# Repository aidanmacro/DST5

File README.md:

---
publishDate: YYYY-MM-DDT00:00:00Z

title: Low-Cost Breath Monitoring for Musicians Using the MYOSA Platform

excerpt: A portable, low-cost respiratory monitoring system for brass and wind musicians using the MYOSA development board, NDIR CO₂ sensing, and environmental measurements.

image: 

tags:
  - Embedded Systems
  - IoT
  - Music Technology
  - Respiratory Monitoring
  - MYOSA
---

> A low-cost embedded system providing objective, real-time respiratory feedback for musicians.

---

## Acknowledgements

---

## Overview

### Project Summary

### Problem Being Solved

### Project Objectives

---

## Demo / Examples

### Images

### Videos

---

## Features (Detailed)

### 1. MYOSA Embedded Platform

### 2. Breath Monitoring System

### 3. BMP180 Environmental Monitoring

### 4. Data Logging

### 5. User Interface

### 6. Low-Cost Design

### 7. Future Improvements

---

## Usage Instructions

### Hardware Setup

### Running the Software

### Example Code

## Tech Stack

---

## Requirements / Installation

### Hardware

### Software

## File Structure (Optional)

---

## License (Optional)

---

## Contribution Notes (Optional)

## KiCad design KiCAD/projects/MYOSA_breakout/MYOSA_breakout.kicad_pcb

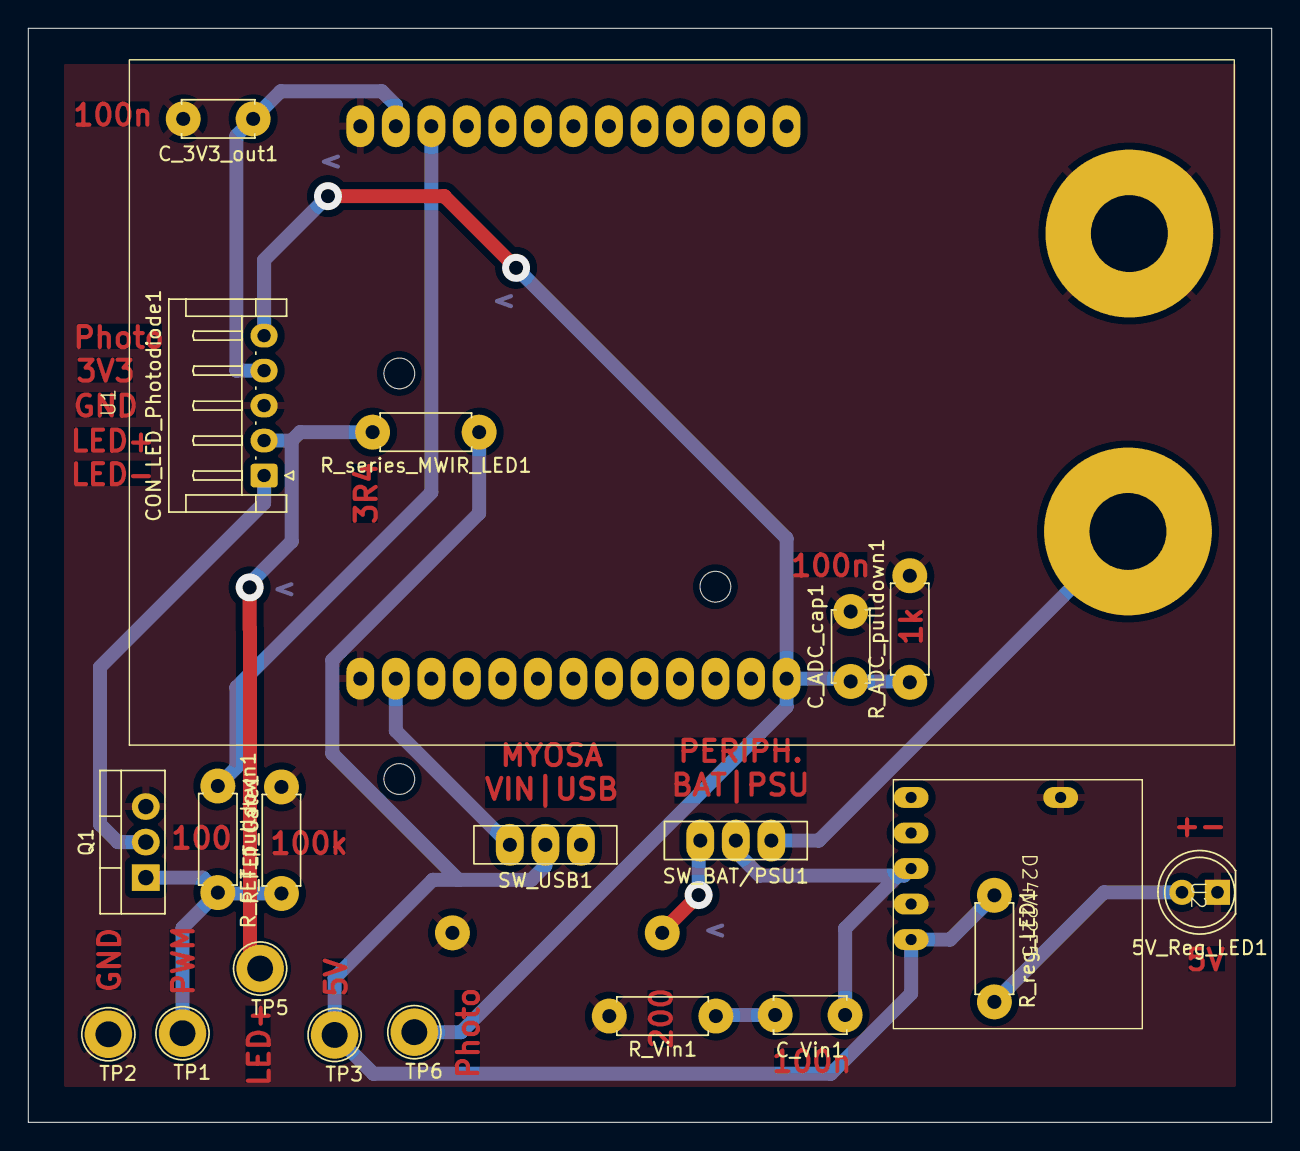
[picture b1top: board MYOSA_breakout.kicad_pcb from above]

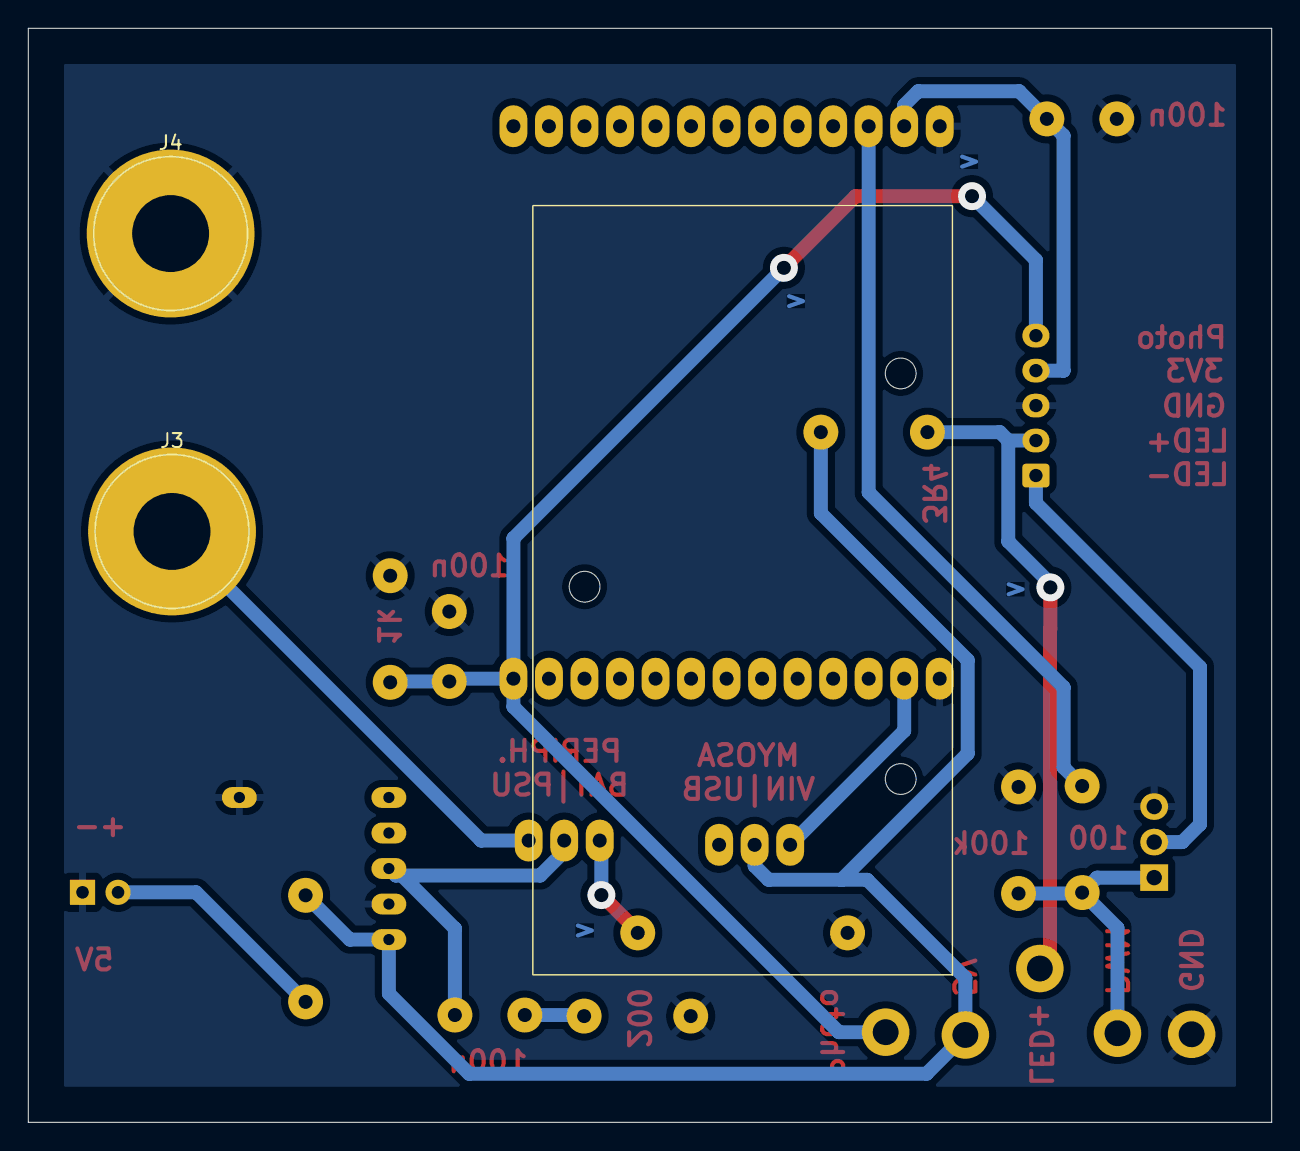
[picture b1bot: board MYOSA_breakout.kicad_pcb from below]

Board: 2 copper layers, 88.9 x 78.2 mm, 24 parts (3 on the bottom side), 14 nets.

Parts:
5V_Reg_LED1: LED; LED_D5.0mm
BT1: Battery; BatteryHolder_MPD_BA9VPC_1xPP3
CON_LED_Photodiode1: Conn_01x05_Socket; JST_EH_S5B-EH_1x05_P2.50mm_Horizontal
C_3V3_out1: C; C_Disc_D5.0mm_W2.5mm_P5.00mm
C_ADC_cap1: 100n; C_Disc_D5.0mm_W2.5mm_P5.00mm
C_Vin1: 100nF; C_Disc_D5.0mm_W2.5mm_P5.00mm
J3: PSU_9V; Banana_Jack_1Pin
J4: PSU_GND; Banana_Jack_1Pin
Q1: IRLZ44N; TO-220-3_Vertical
R_ADC_pulldown1: 1K; R_Axial_DIN0207_L6.3mm_D2.5mm_P7.62mm_Horizontal
R_FET_Gate1: 100R; R_Axial_DIN0207_L6.3mm_D2.5mm_P7.62mm_Horizontal
R_FET_pulldown1: 100k; R_Axial_DIN0207_L6.3mm_D2.5mm_P7.62mm_Horizontal
R_Vin1: 200; R_Axial_DIN0207_L6.3mm_D2.5mm_P7.62mm_Horizontal
R_reg_LED1: 200; R_Axial_DIN0207_L6.3mm_D2.5mm_P7.62mm_Horizontal
R_series_MWIR_LED1: 3.4R; R_Axial_DIN0207_L6.3mm_D2.5mm_P7.62mm_Horizontal
SW_BAT/PSU1: Batt/PSU_switch; SW_Slide-03_Wuerth-WS-SLTV_10x2.5x6.4_P2.54mm
SW_USB1: USB/REG_switch; SW_Slide-03_Wuerth-WS-SLTV_10x2.5x6.4_P2.54mm
TP1: PWM_TestPoint; TestPoint_Loop_D2.50mm_Drill1.85mm
TP2: GND_TestPoint; TestPoint_Loop_D2.50mm_Drill1.85mm
TP3: 5V_TestPoint; TestPoint_Loop_D2.50mm_Drill1.85mm
TP5: LED_Anode_TestPoint; TestPoint_Loop_D2.50mm_Drill1.85mm
TP6: PhotoIn_TestPoint; TestPoint_Loop_D2.50mm_Drill1.85mm
U1: MYOSA_ESP-32
U2: D24V22F5

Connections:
/3V3_OUT: CON_LED_Photodiode1.4, C_3V3_out1.1, U1.25 (3V3)
/5V: R_reg_LED1.1, R_series_MWIR_LED1.1, SW_USB1.2 (B), TP3.1, U2.5 (VOUT)
/LED_Anode: CON_LED_Photodiode1.2, R_series_MWIR_LED1.2, TP5.1
/LED_Cathode: CON_LED_Photodiode1.1, Q1.2 (D)
/PWM: R_FET_Gate1.1, U1.24 (D4)
/Photo_IN: CON_LED_Photodiode1.5, C_ADC_cap1.1, R_ADC_pulldown1.1, TP6.1, U1.13 (VP)
/Vin_SRC: C_Vin1.1, SW_BAT/PSU1.2 (B), U2.3 (VIN)
GND: 5V_Reg_LED1.1 (K), BT1.2 (-), CON_LED_Photodiode1.3, C_3V3_out1.2, C_ADC_cap1.2, J4.1, Q1.3 (S), R_ADC_pulldown1.2, R_FET_pulldown1.2, R_Vin1.2, TP2.1, U1.1 (GND), U1.26 (GND), U2.4 (GND), U2.6 (GND)
unnamed: 5V_Reg_LED1.2 (A), R_reg_LED1.2
unnamed: BT1.1 (+), SW_BAT/PSU1.3 (C)
unnamed: C_Vin1.2, R_Vin1.1
unnamed: J3.1, SW_BAT/PSU1.1 (A)
unnamed: Q1.1 (G), R_FET_Gate1.2, R_FET_pulldown1.1, TP1.1
unnamed: SW_USB1.3 (C), U1.2 (VIN)

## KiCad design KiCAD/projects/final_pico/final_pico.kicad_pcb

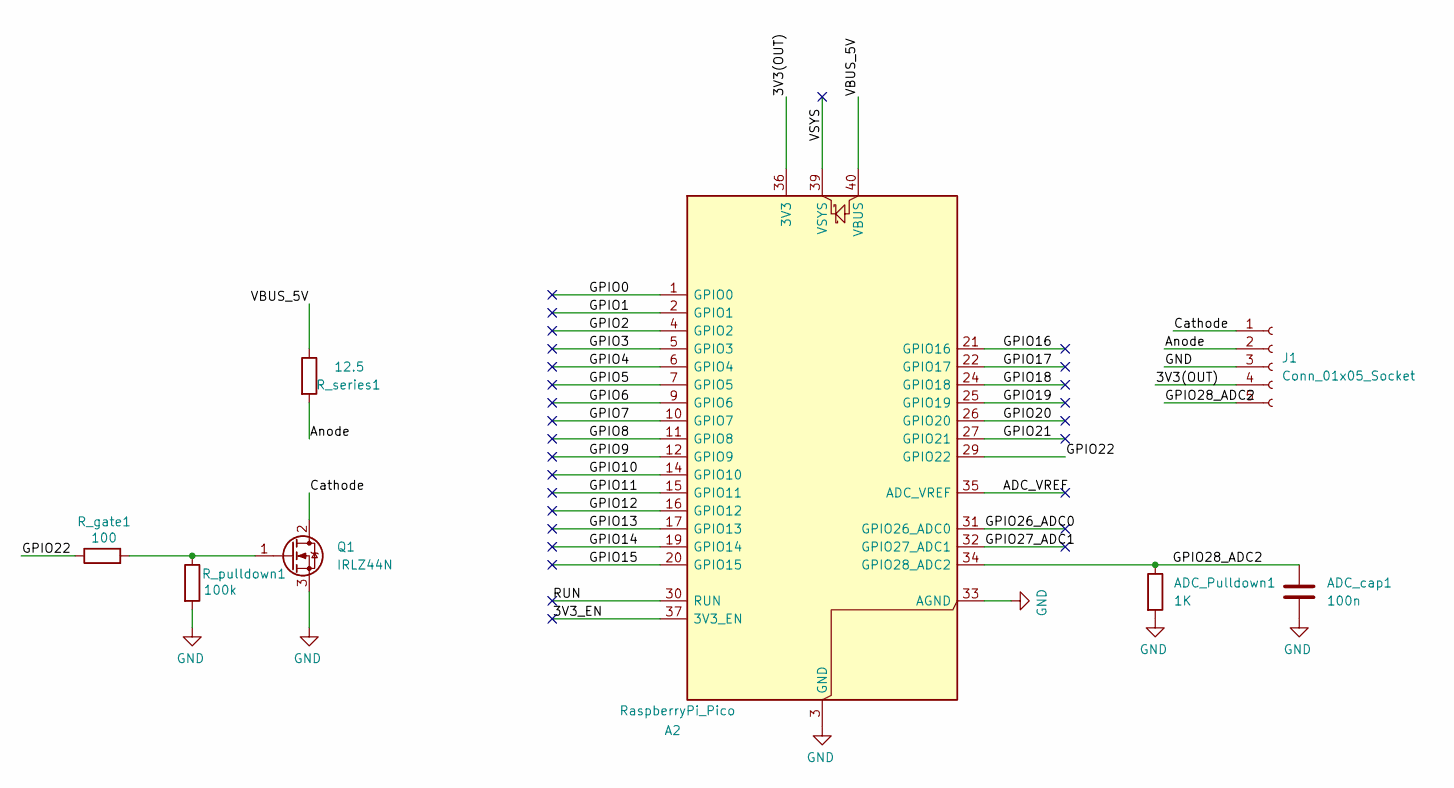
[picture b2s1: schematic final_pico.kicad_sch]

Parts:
A2: RaspberryPi_Pico; RaspberryPi_Pico_Common_THT
ADC_Pulldown1: 1K; R_Axial_DIN0207_L6.3mm_D2.5mm_P7.62mm_Horizontal
ADC_cap1: 100n; C_Disc_D5.0mm_W2.5mm_P5.00mm
J1: Conn_01x05_Socket; JST_EH_S5B-EH_1x05_P2.50mm_Horizontal
Q1: IRLZ44N; TO-220-3_Vertical
R_gate1: 100; R_Axial_DIN0207_L6.3mm_D2.5mm_P7.62mm_Horizontal
R_pulldown1: 100k; R_Axial_DIN0207_L6.3mm_D2.5mm_P7.62mm_Horizontal
R_series1: 12.5; R_Axial_DIN0207_L6.3mm_D2.5mm_P7.62mm_Horizontal

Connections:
/3V3(OUT): A2.36 (3V3), J1.4
/3V3_EN: A2.37 (3V3_EN)
/ADC_VREF: A2.35 (ADC_VREF)
/Anode: J1.2, R_series1.2
/Cathode: J1.1, Q1.2 (D)
/GPIO0: A2.1 (GPIO0)
/GPIO1: A2.2 (GPIO1)
/GPIO2: A2.4 (GPIO2)
/GPIO3: A2.5 (GPIO3)
/GPIO4: A2.6 (GPIO4)
/GPIO5: A2.7 (GPIO5)
/GPIO6: A2.9 (GPIO6)
/GPIO7: A2.10 (GPIO7)
/GPIO8: A2.11 (GPIO8)
/GPIO9: A2.12 (GPIO9)
/GPIO10: A2.14 (GPIO10)
/GPIO11: A2.15 (GPIO11)
/GPIO12: A2.16 (GPIO12)
/GPIO13: A2.17 (GPIO13)
/GPIO14: A2.19 (GPIO14)
/GPIO15: A2.20 (GPIO15)
/GPIO16: A2.21 (GPIO16)
/GPIO17: A2.22 (GPIO17)
/GPIO18: A2.24 (GPIO18)
/GPIO19: A2.25 (GPIO19)
/GPIO20: A2.26 (GPIO20)
/GPIO21: A2.27 (GPIO21)
/GPIO22: A2.29 (GPIO22), R_gate1.1
/GPIO26_ADC0: A2.31 (GPIO26_ADC0)
/GPIO27_ADC1: A2.32 (GPIO27_ADC1)
/GPIO28_ADC2: A2.34 (GPIO28_ADC2), ADC_Pulldown1.1, ADC_cap1.1, J1.5
/RUN: A2.30 (RUN)
/VBUS_5V: A2.40 (VBUS), R_series1.1
/VSYS: A2.39 (VSYS)
GND: A2.3 (GND), A2.8 (GND), A2.13 (GND), A2.18 (GND), A2.23 (GND), A2.28 (GND), A2.33 (AGND), A2.38 (GND), ADC_Pulldown1.2, ADC_cap1.2, J1.3, Q1.3 (S), R_pulldown1.2
unnamed: Q1.1 (G), R_gate1.2, R_pulldown1.1

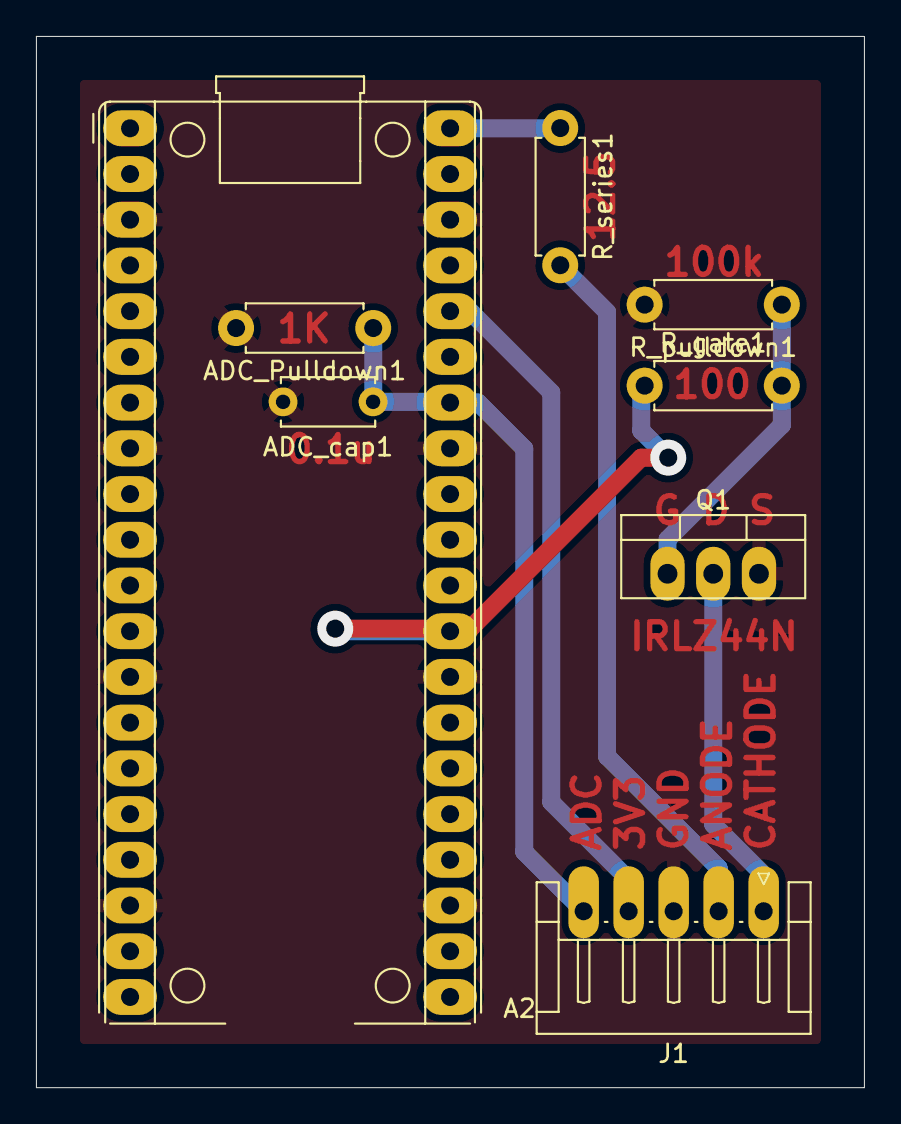
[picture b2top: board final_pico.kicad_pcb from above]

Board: 2 copper layers, 46.0 x 58.4 mm, 8 parts (0 on the bottom side), 8 nets.

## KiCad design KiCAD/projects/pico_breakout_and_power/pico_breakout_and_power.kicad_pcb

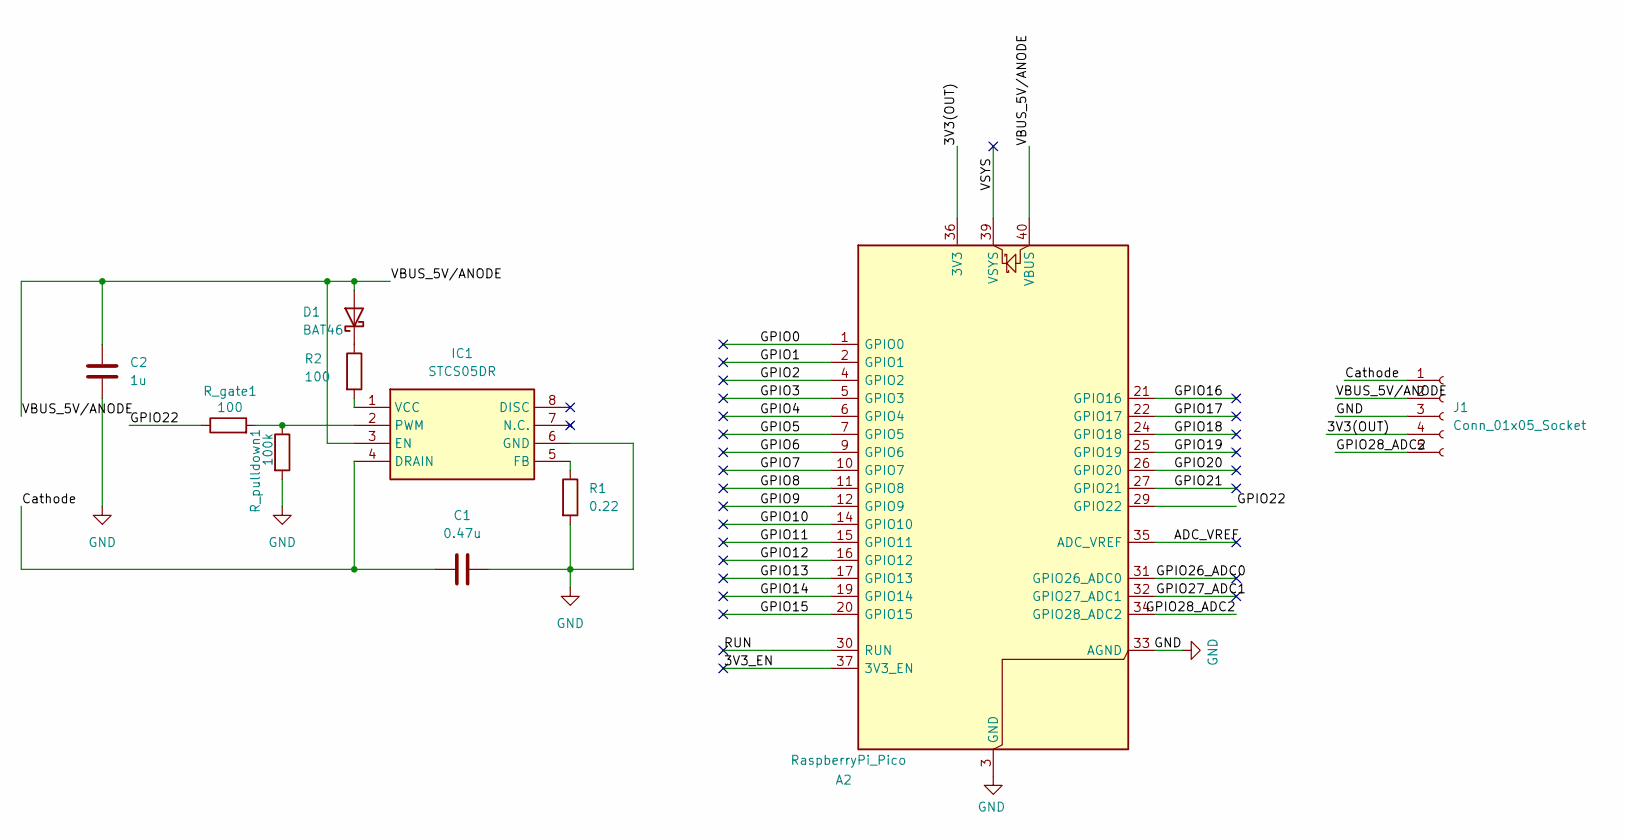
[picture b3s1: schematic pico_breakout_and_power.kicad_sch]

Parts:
A2: RaspberryPi_Pico; RaspberryPi_Pico_Common_THT
C1: 0.47u; C_Disc_D10.5mm_W5.0mm_P10.00mm
C2: 1u; C_Disc_D10.5mm_W5.0mm_P10.00mm
D1: BAT46; D_DO-35_SOD27_P7.62mm_Horizontal
IC1: STCS05DR; SOIC127P600X175-8N; Mouser Part Number 511-STCS05DR
J1: Conn_01x05_Socket; JST_EH_S5B-EH_1x05_P2.50mm_Horizontal
R1: 0.22; R_Axial_DIN0411_L9.9mm_D3.6mm_P12.70mm_Horizontal
R2: 100; R_Axial_DIN0207_L6.3mm_D2.5mm_P10.16mm_Horizontal
R_gate1: 100; R_Axial_DIN0207_L6.3mm_D2.5mm_P10.16mm_Horizontal
R_pulldown1: 100k; R_Axial_DIN0207_L6.3mm_D2.5mm_P10.16mm_Horizontal

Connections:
/3V3(OUT): A2.36 (3V3), J1.4
/3V3_EN: A2.37 (3V3_EN)
/ADC_VREF: A2.35 (ADC_VREF)
/Cathode: C1.1, IC1.4 (DRAIN), J1.1
/GPIO0: A2.1 (GPIO0)
/GPIO1: A2.2 (GPIO1)
/GPIO2: A2.4 (GPIO2)
/GPIO3: A2.5 (GPIO3)
/GPIO4: A2.6 (GPIO4)
/GPIO5: A2.7 (GPIO5)
/GPIO6: A2.9 (GPIO6)
/GPIO7: A2.10 (GPIO7)
/GPIO8: A2.11 (GPIO8)
/GPIO9: A2.12 (GPIO9)
/GPIO10: A2.14 (GPIO10)
/GPIO11: A2.15 (GPIO11)
/GPIO12: A2.16 (GPIO12)
/GPIO13: A2.17 (GPIO13)
/GPIO14: A2.19 (GPIO14)
/GPIO15: A2.20 (GPIO15)
/GPIO16: A2.21 (GPIO16)
/GPIO17: A2.22 (GPIO17)
/GPIO18: A2.24 (GPIO18)
/GPIO19: A2.25 (GPIO19)
/GPIO20: A2.26 (GPIO20)
/GPIO21: A2.27 (GPIO21)
/GPIO22: A2.29 (GPIO22), R_gate1.1
/GPIO26_ADC0: A2.31 (GPIO26_ADC0)
/GPIO27_ADC1: A2.32 (GPIO27_ADC1)
/GPIO28_ADC2: A2.34 (GPIO28_ADC2), J1.5
/RUN: A2.30 (RUN)
/VBUS_5V/ANODE: A2.40 (VBUS), C2.1, D1.2 (A), IC1.3 (EN), J1.2
/VSYS: A2.39 (VSYS)
GND: A2.3 (GND), A2.8 (GND), A2.13 (GND), A2.18 (GND), A2.23 (GND), A2.28 (GND), A2.33 (AGND), A2.38 (GND), C1.2, C2.2, IC1.6 (GND), J1.3, R1.2, R_pulldown1.2
unnamed: D1.1 (K), R2.1
unnamed: IC1.5 (FB), R1.1
unnamed: IC1.2 (PWM), R_gate1.2, R_pulldown1.1
unnamed: IC1.1 (VCC), R2.2

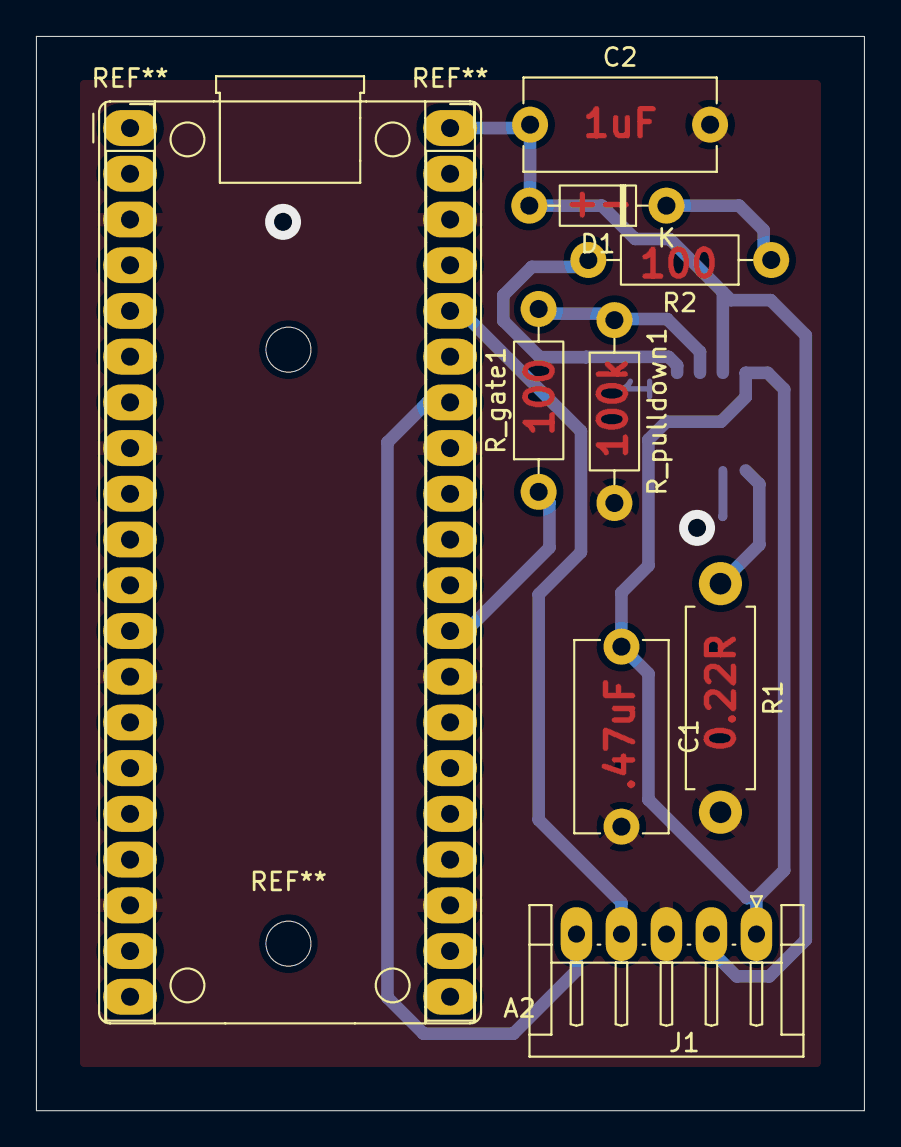
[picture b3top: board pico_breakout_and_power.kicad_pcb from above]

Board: 2 copper layers, 46.0 x 59.7 mm, 10 parts (1 on the bottom side), 10 nets.

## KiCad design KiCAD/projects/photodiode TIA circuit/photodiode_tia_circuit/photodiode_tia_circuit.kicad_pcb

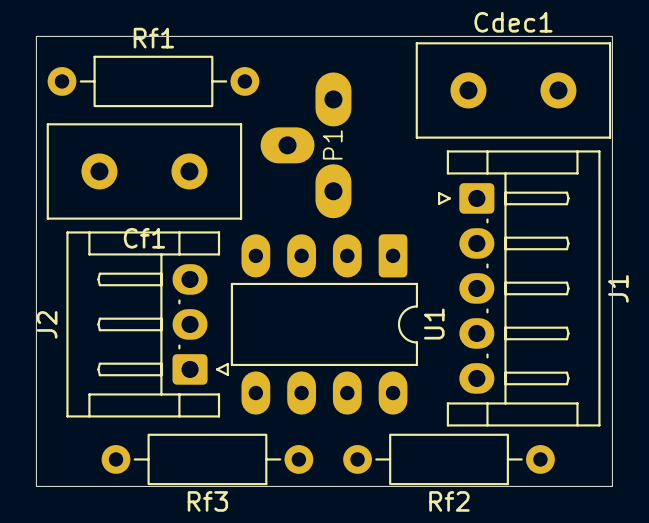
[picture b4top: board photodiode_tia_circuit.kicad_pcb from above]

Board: 2 copper layers, 32.0 x 25.0 mm, 9 parts (0 on the bottom side), 8 nets, no tracks yet.

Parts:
Cdec1: 0.1uF; C_Disc_D10.5mm_W5.0mm_P5.00mm
Cf1: 2pF; C_Disc_D10.5mm_W5.0mm_P5.00mm
J1: Conn_01x05_Socket; JST_EH_S5B-EH_1x05_P2.50mm_Horizontal
J2: Conn_01x03_Socket; JST_EH_S3B-EH_1x03_P2.50mm_Horizontal
P1: TO46_3PIN
Rf1: 470k; R_Axial_DIN0207_L6.3mm_D2.5mm_P10.16mm_Horizontal
Rf2: 100k; R_Axial_DIN0207_L6.3mm_D2.5mm_P10.16mm_Horizontal
Rf3: 1.8k; R_Axial_DIN0207_L6.3mm_D2.5mm_P10.16mm_Horizontal
U1: MCP6292; DIP-8_W7.62mm_LongPads

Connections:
+3.3V: Cdec1.1, J1.4, U1.8 (V+)
GND: Cdec1.2, J1.5, J2.2, P1.2 (GND), P1.3 (Anode), Rf3.2, U1.3 (+), U1.4 (V-)
unnamed: J1.1, J2.3
unnamed: J1.2, J2.1
unnamed: J1.3, Rf2.1, U1.7
unnamed: Cf1.1, P1.1 (Cathode), Rf1.2, U1.2 (-)
unnamed: Cf1.2, Rf1.1, U1.1, U1.5 (+)
unnamed: Rf2.2, Rf3.1, U1.6 (-)

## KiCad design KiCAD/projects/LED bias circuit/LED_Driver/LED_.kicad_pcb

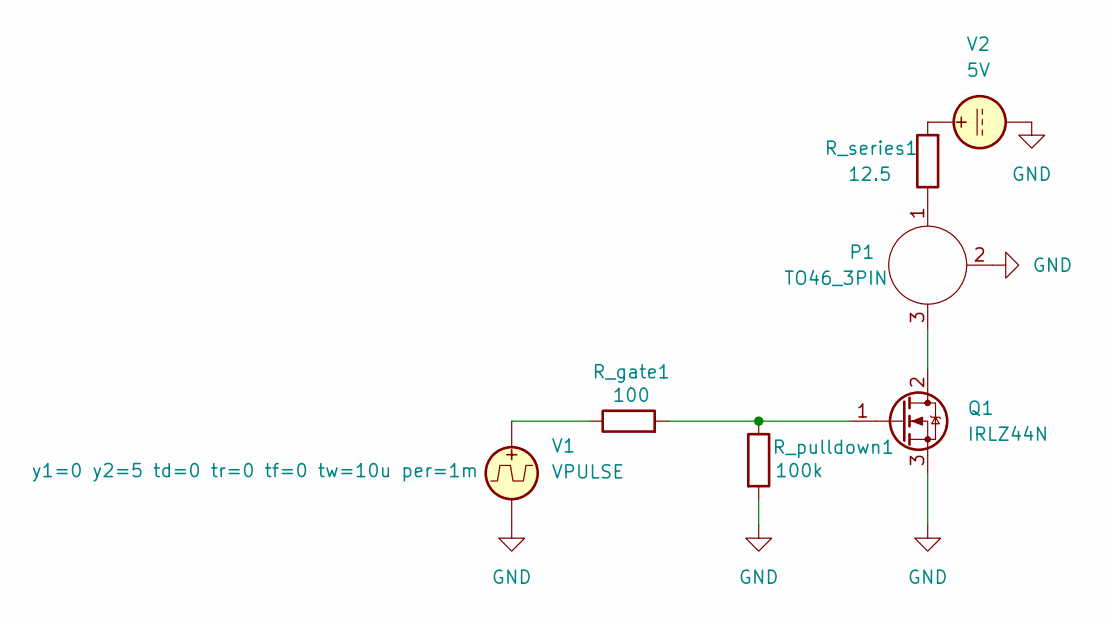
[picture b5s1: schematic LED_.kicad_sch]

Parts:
P1: TO46_3PIN
Q1: IRLZ44N; TO-220-3_Vertical
R_gate1: 100; R_Axial_DIN0207_L6.3mm_D2.5mm_P10.16mm_Horizontal
R_pulldown1: 100k; R_Axial_DIN0207_L6.3mm_D2.5mm_P10.16mm_Horizontal
R_series1: 12.5; R_Axial_DIN0207_L6.3mm_D2.5mm_P10.16mm_Horizontal
V1: VPULSE; TerminalBlock_Phoenix_MKDS-1,5-2-5.08_1x02_P5.08mm_Horizont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
V2: 5V; TerminalBlock_Phoenix_MKDS-1,5-2-5.08_1x02_P5.08mm_Horizont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

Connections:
GND: P1.2 (GND), Q1.3 (S), R_pulldown1.2, V1.2, V2.2
unnamed: P1.1 (Anode), R_series1.1
unnamed: P1.3 (Cathode), Q1.2 (D)
unnamed: Q1.1 (G), R_gate1.2, R_pulldown1.1
unnamed: R_gate1.1, V1.1
unnamed: R_series1.2, V2.1

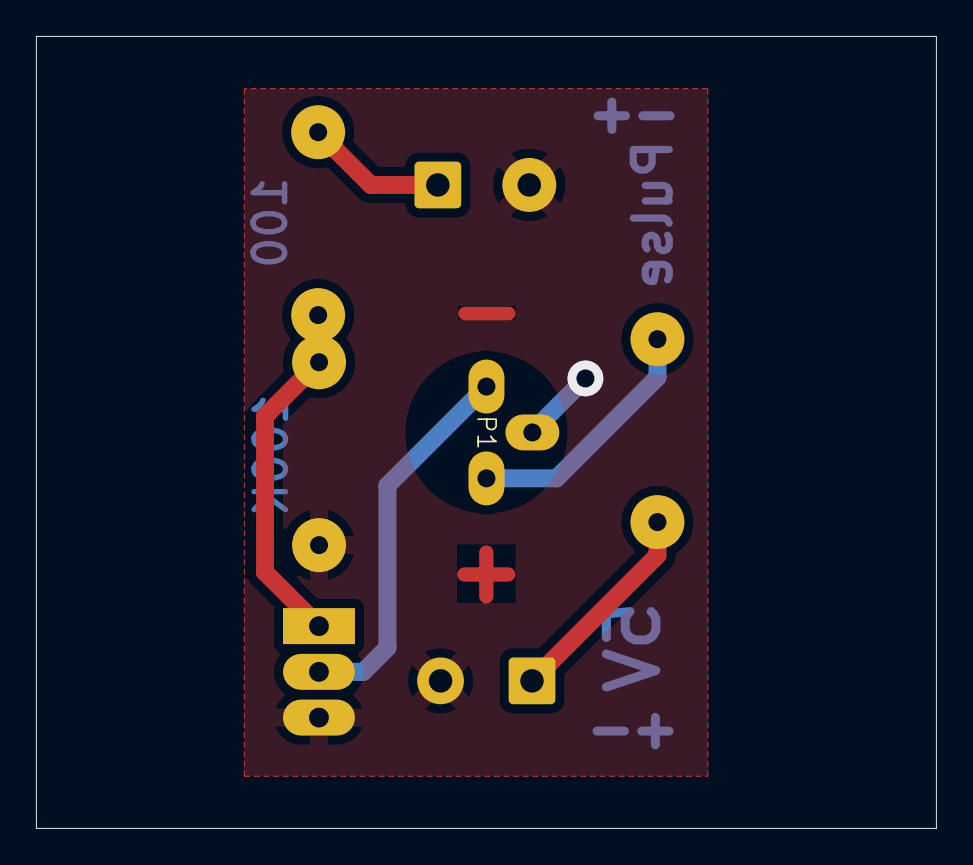
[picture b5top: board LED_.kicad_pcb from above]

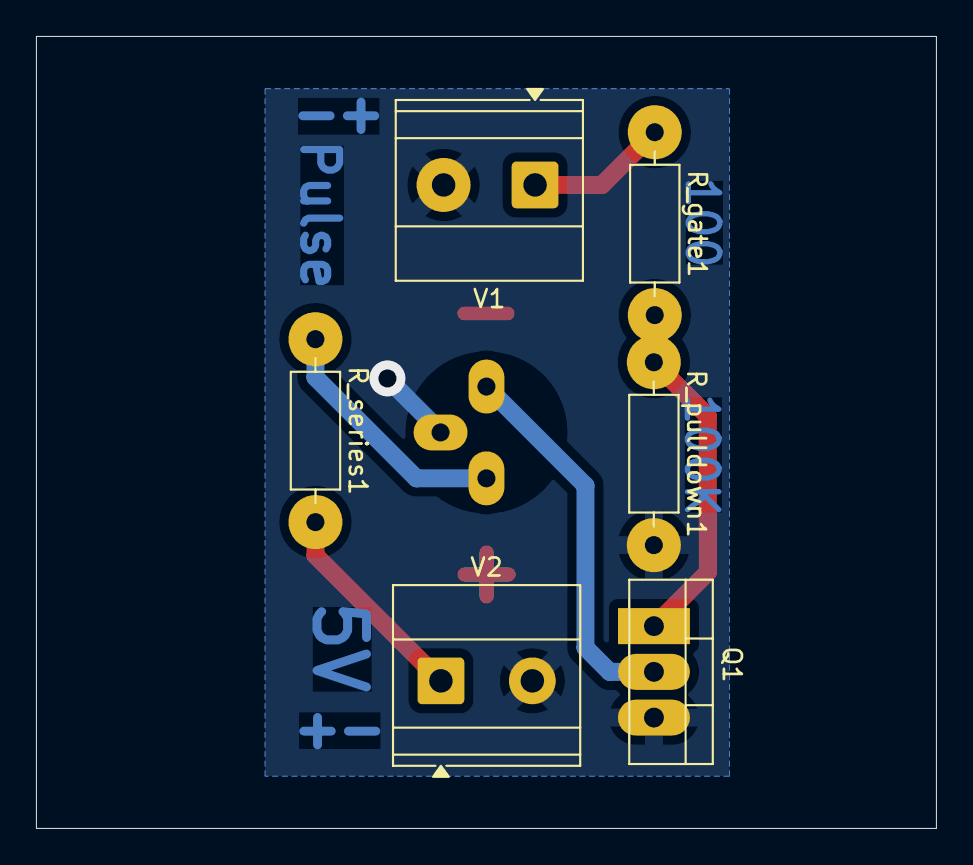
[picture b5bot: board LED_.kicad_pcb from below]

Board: 2 copper layers, 50.0 x 44.0 mm, 7 parts (6 on the bottom side), 6 nets.

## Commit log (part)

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2026-04-22 First commit with custom 3-pin socker footprint and symbol.
2026-04-22 Create README.md for DST5 KiCad Library
    Add initial README with library information and setup instructions.
2026-04-24 test commit adding contributor
2026-04-24 Add project folder with LED circuit
2026-04-29 edited tO46 symbol to be correct
2026-05-01 Fix size of TO46 socket
2026-05-06 New project for pico breakout board
2026-05-07 Add proper board edge
2026-05-07 manufacture documents and 3d model step file
2026-05-07 add pi pico footprint library as submodule
2026-05-07 Made grouped 3d model of pico with sockets
2026-05-07 Added new LED driver circuit design and associated KiCAD library files. to DST custom library.
2026-05-07 Added 3D files for the TO46 package to the custom DST library
2026-05-07 Fixed the weird holes in TO46 sheath 3D models, and the orientation too :p
2026-05-07 Added 3D model for the STCS05 driver to custom DST library
2026-05-07 Combining pico and LED driver circuits
2026-05-08 Routed combined pico board
2026-05-08 First version of pico breakout submitted for manufacturing. Thicker traces and pads
2026-05-09 Made simulation of TIA circuit
2026-05-09 Update to make more sense and have flat-topped pulses
2026-05-09 Better yet sim
2026-05-09 removed history tracking
2026-05-09 even better sims
2026-05-11 Corrected photomasks for pico pcb
2026-05-11 latest version
2026-05-12 Add C code to generate pulse, monitor adc, and send data via usb on pico. Also Python code to plot it in realtime on different device
2026-05-14 final C scripts for pico code and external python plotting
2026-05-14 Merge
2026-05-14 Remove .history folders from tracking
2026-05-14 Stop tracking .history folders
2026-05-14 Refreshing repo
2026-05-14 Deleting copy
2026-05-14 Final Pico breakout board.
2026-05-18 Cmake files for pico code
2026-05-19 latest TIA
2026-05-19 Added code for plotting csvs from scopes, and refined pico and realtime plotting code further.
2026-05-21 final spectogram and capnographs code.
2026-05-25 final pcb cleanups
